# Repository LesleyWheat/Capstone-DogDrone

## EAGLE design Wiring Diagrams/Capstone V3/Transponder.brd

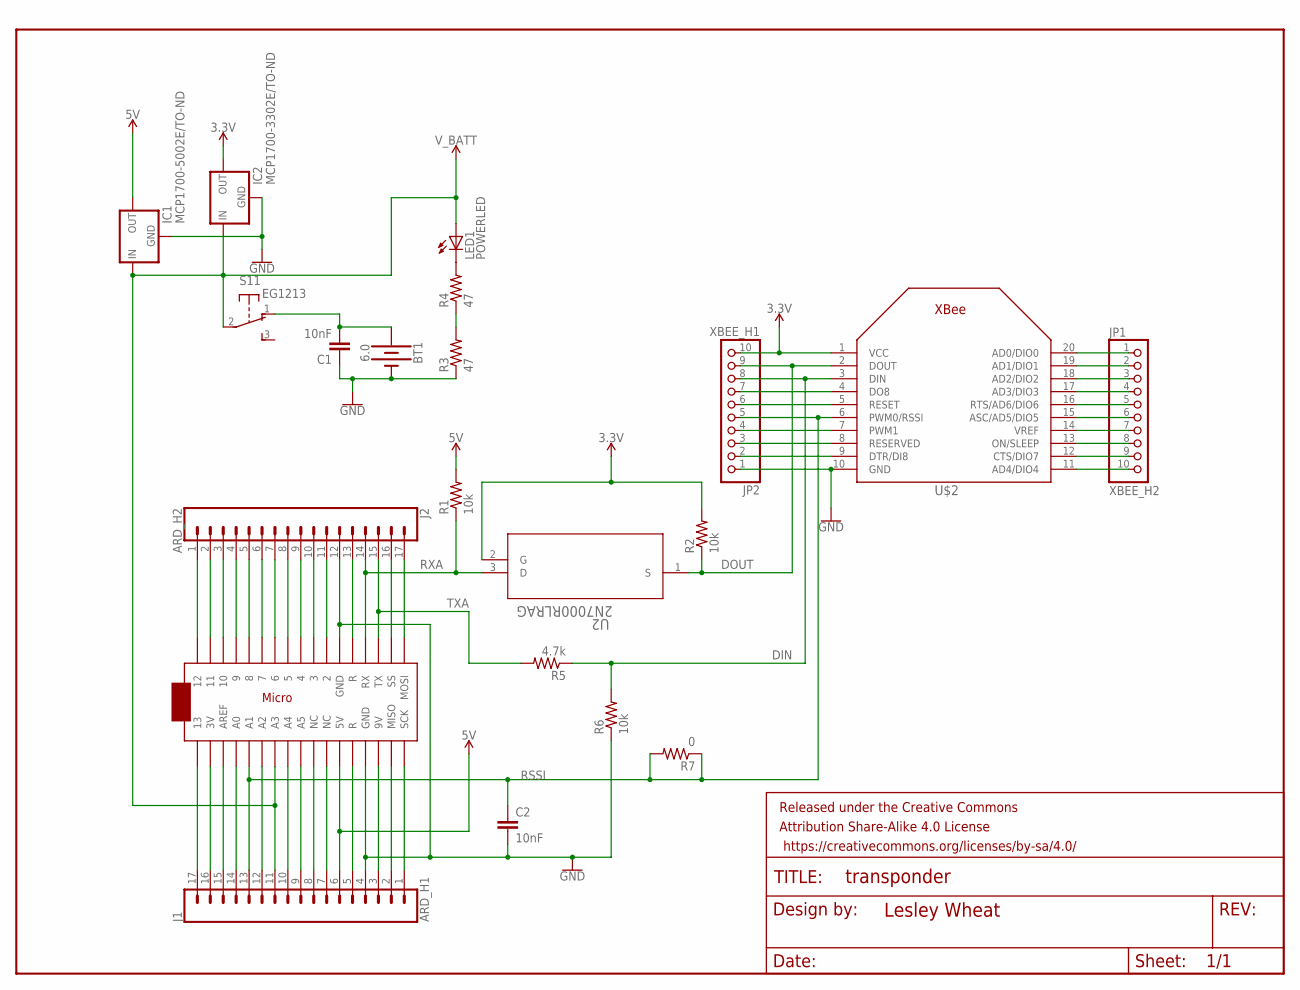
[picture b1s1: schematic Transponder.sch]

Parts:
BT1: 6.0; BATTCON_20MM_4LEGS
C1, C2: 10nF; CAP-PTH-10MM
FRAME1: FRAME-LETTERNO_PACKAGE; DUMMY
IC1: MCP1700-5002E/TO-ND; TO92-INLINE
IC2: MCP1700-3302E/TO-ND; TO92-INLINE
J1: ARD_H1; 1X17_NO_SILK
J2: ARD_H2; 1X17_NO_SILK
JP1: XBEE_H2; 1X10M
JP2: XBEE_H1; 1X10M
LED1: POWERLED; LED5MM
R1, R2, R6: 10k; 0207/12
R3, R4: 47; 0207/12
R5: 4.7k; 0207/12
R7: 0; 0207/12
S1: EG1213
U2: 2N7000RLRAG; TO-92
U$1: ARDUINOMICRO
U$2: XBEE

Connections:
3.3V: IC2.3 (OUT), JP2.10, R2.2, U2.2 (G), U$2.1 (VCC)
5V: IC1.3 (OUT), J1.6, R1.2, U$1.P$23 (5V)
DIN: JP2.8, R5.1, R6.2, U$2.3 (DIN)
DOUT: JP2.9, R2.1, U2.1 (S), U$2.2 (DOUT)
GND: BT1.NEGATIVE (-), C1.1, C2.2, IC1.1 (GND), IC2.1 (GND), J1.4, J2.12, JP2.1, R3.1, R6.1, U$1.P$12 (GND), U$1.P$21 (GND), U$2.10 (GND)
unnamed: BT1.POSITIVE@1 (+), BT1.POSITIVE@2 (+), BT1.POSITIVE@3 (+), BT1.POSITIVE@4 (+), C1.2, S1.1 (O)
unnamed: JP2.3, U$2.8 (RESERVED)
unnamed: J1.14, U$1.P$31 (A0)
unnamed: LED1.K (C), R4.2
unnamed: R3.2, R4.1
unnamed: J1.17, U$1.P$34 (13)
unnamed: J1.15, U$1.P$32 (AREF)
unnamed: J1.12, U$1.P$29 (A2)
unnamed: J1.9, U$1.P$26 (A5)
unnamed: J1.10, U$1.P$27 (A4)
unnamed: J1.8, U$1.P$25 (NC)
unnamed: J1.7, U$1.P$24 (NC)
unnamed: J1.5, U$1.P$13 (R)
unnamed: J1.3, U$1.P$20 (9V)
unnamed: J1.2, U$1.P$19 (MISO)
unnamed: J1.1, U$1.P$18 (SCK)
unnamed: J2.17, U$1.P$17 (MOSI)
unnamed: J2.16, U$1.P$16 (SS)
unnamed: J2.13, U$1.P$22 (R)
unnamed: J2.11, U$1.P$11 (2)
unnamed: J2.10, U$1.P$10 (3)
unnamed: J2.9, U$1.P$9 (4)
unnamed: J2.7, U$1.P$7 (6)
unnamed: J2.8, U$1.P$8 (5)
unnamed: JP1.1, U$2.20 (AD0/DIO0)
unnamed: J2.6, U$1.P$6 (7)
unnamed: J2.5, U$1.P$5 (8)
unnamed: J2.4, U$1.P$4 (9)
unnamed: J2.3, U$1.P$3 (10)
unnamed: J2.2, U$1.P$2 (11)
unnamed: J2.1, U$1.P$1 (12)
unnamed: J1.16, U$1.P$33 (3V)
unnamed: JP1.2, U$2.19 (AD1/DIO1)
unnamed: JP1.3, U$2.18 (AD2/DIO2)
unnamed: JP1.4, U$2.17 (AD3/DIO3)
unnamed: JP1.5, U$2.16 (RTS/AD6/DIO6)
unnamed: JP1.6, U$2.15 (ASC/AD5/DIO5)
unnamed: JP1.7, U$2.14 (VREF)
unnamed: JP1.8, U$2.13 (ON/SLEEP)
unnamed: JP1.9, U$2.12 (CTS/DIO7)
unnamed: JP1.10, U$2.11 (AD4/DIO4)
unnamed: JP2.2, U$2.9 (DTR/DI8)
unnamed: JP2.4, U$2.7 (PWM1)
unnamed: JP2.6, U$2.5 (RESET)
unnamed: JP2.7, U$2.4 (DO8)
RSSI: C2.1, J1.13, JP2.5, R7.1, R7.2, U$1.P$30 (A1), U$2.6 (PWM0/RSSI)
RXA: J2.14, R1.1, U2.3 (D), U$1.P$14 (RX)
TXA: J2.15, R5.2, U$1.P$15 (TX)
V_BATT: IC1.2 (IN), IC2.2 (IN), J1.11, LED1.A, S1.2, U$1.P$28 (A3)

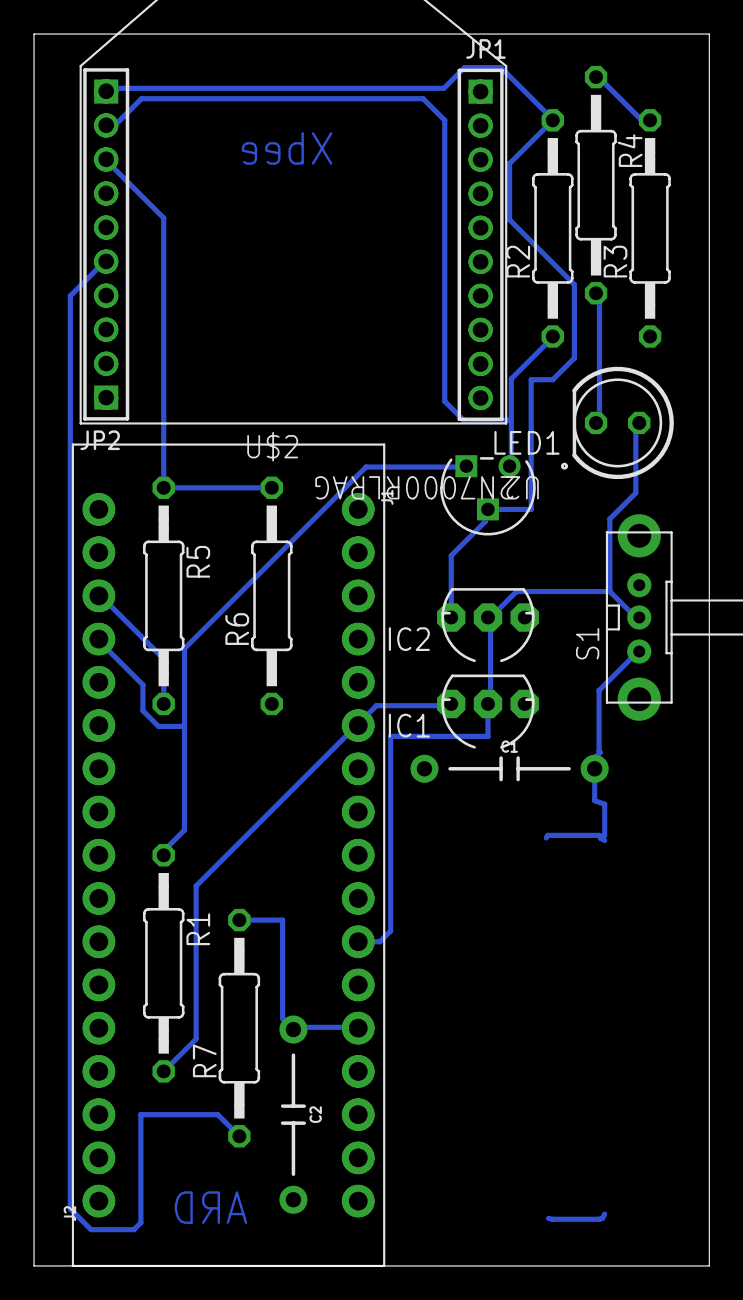
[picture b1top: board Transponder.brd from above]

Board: 2 copper layers, 39.7 x 72.4 mm, 22 parts (1 on the bottom side), 54 nets.

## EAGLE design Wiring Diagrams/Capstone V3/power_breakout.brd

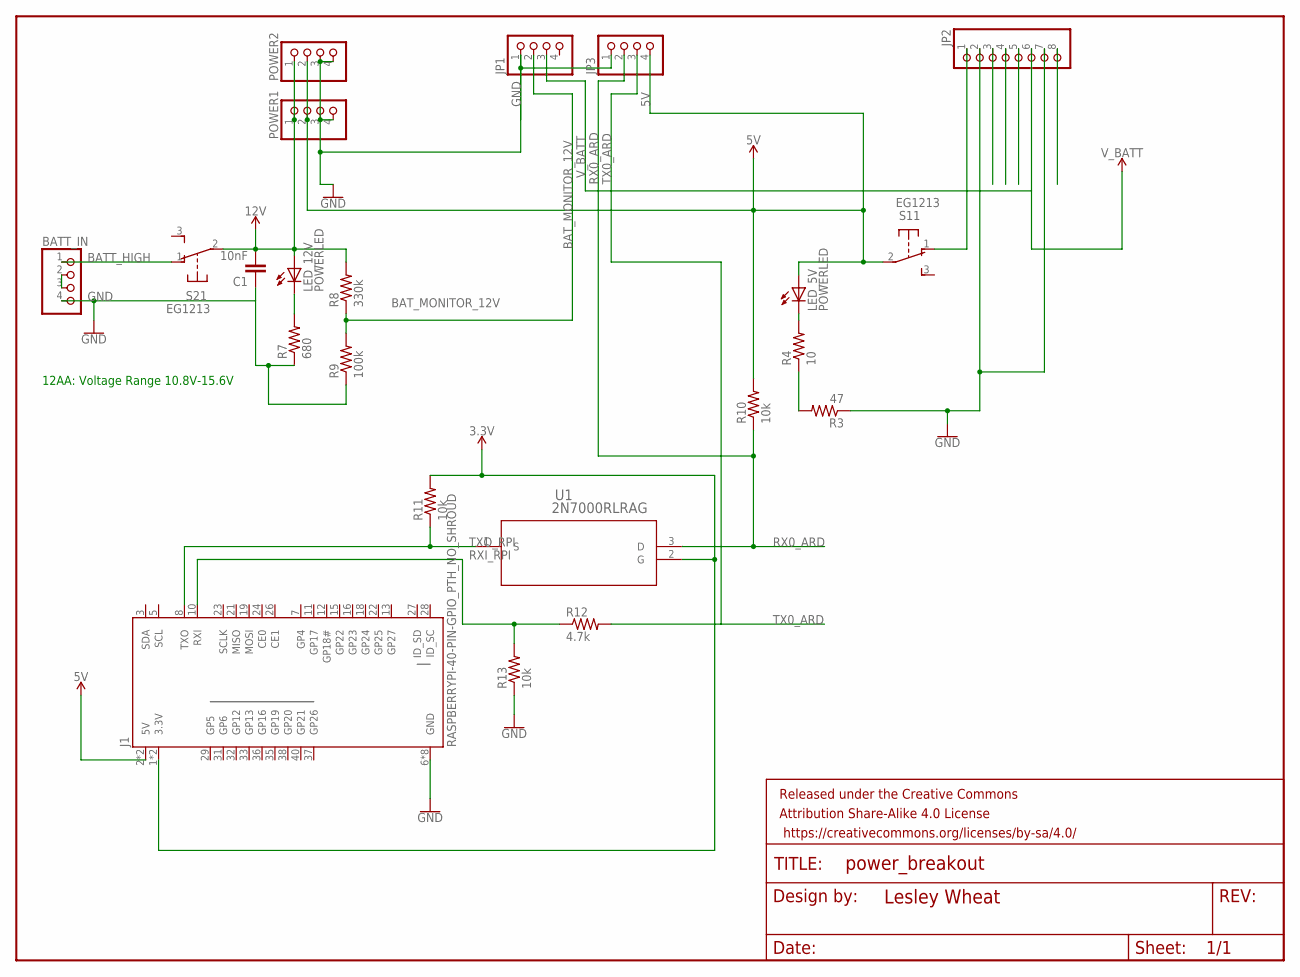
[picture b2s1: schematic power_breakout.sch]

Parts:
BATT_IN: PINHD-1X4; 1X04
C1: 10nF; CAP-PTH-10MM
FRAME1: FRAME-LETTERNO_PACKAGE; DUMMY
J1: RASPBERRYPI-40-PIN-GPIO_PTH_NO_SHROUD; 2X20
JP1, JP3: PINHD-1X4; 1X04
JP2: PINHD-1X8; 1X08
LED_5V, LED_12V: POWERLED; LED5MM
POWER1, POWER2: PINHD-1X4; 1X04
R3: 47; 0207/12
R4: 10; 0207/12
R7: 680; 0207/12
R8: 330k; 0207/12
R9: 100k; 0207/12
R10, R11, R13: 10k; 0207/12
R12: 4.7k; 0207/12
S1, S2: EG1213
U1: 2N7000RLRAG; TO-92

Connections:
3.3V: J1.1 (3.3V), J1.17 (3.3V), R11.2, U1.2 (G)
5V: J1.2 (5V), J1.4 (5V), JP3.4, LED_5V.A, POWER1.2, POWER2.2, R10.2, S1.2
12V: C1.2, LED_12V.A, POWER1.1, POWER2.1, R8.2, S2.2
BATT_HIGH: BATT_IN.1, S2.1 (O)
BAT_MONITOR_12V: JP1.2, R8.1, R9.2
GND: BATT_IN.4, C1.1, J1.6 (GND), J1.9 (GND), J1.14 (GND), J1.20 (GND), J1.25 (GND), J1.30 (GND), J1.34 (GND), J1.39 (GND), JP1.1, JP2.2, JP2.7, JP3.1, POWER1.3, POWER1.4, POWER2.3, POWER2.4, R3.1, R7.1, R9.1, R13.1
unnamed: BATT_IN.2, BATT_IN.3
unnamed: LED_12V.K (C), R7.2
unnamed: JP2.1, S1.1 (O)
unnamed: LED_5V.K (C), R4.2
unnamed: R3.2, R4.1
RX0_ARD: JP3.2, R10.1, U1.3 (D)
RXI_RPI: J1.10 (RXI), R12.1, R13.2
TX0_ARD: JP3.3, R12.2
TXO_RPI: J1.8 (TXO), R11.1, U1.1 (S)
V_BATT: JP1.3, JP2.6

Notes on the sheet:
12AA: Voltage Range 10.8V-15.6V

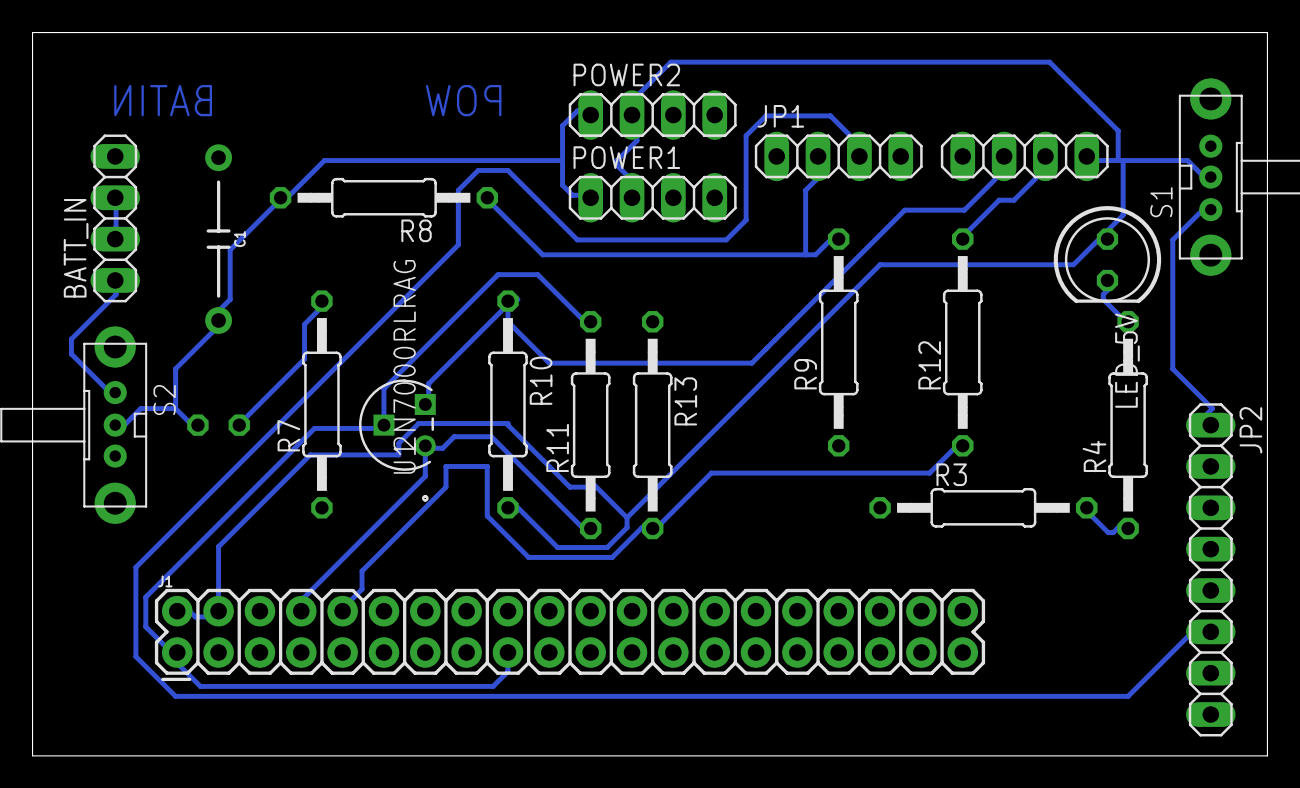
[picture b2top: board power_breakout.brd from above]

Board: 2 copper layers, 75.9 x 44.4 mm, 23 parts (1 on the bottom side), 16 nets.

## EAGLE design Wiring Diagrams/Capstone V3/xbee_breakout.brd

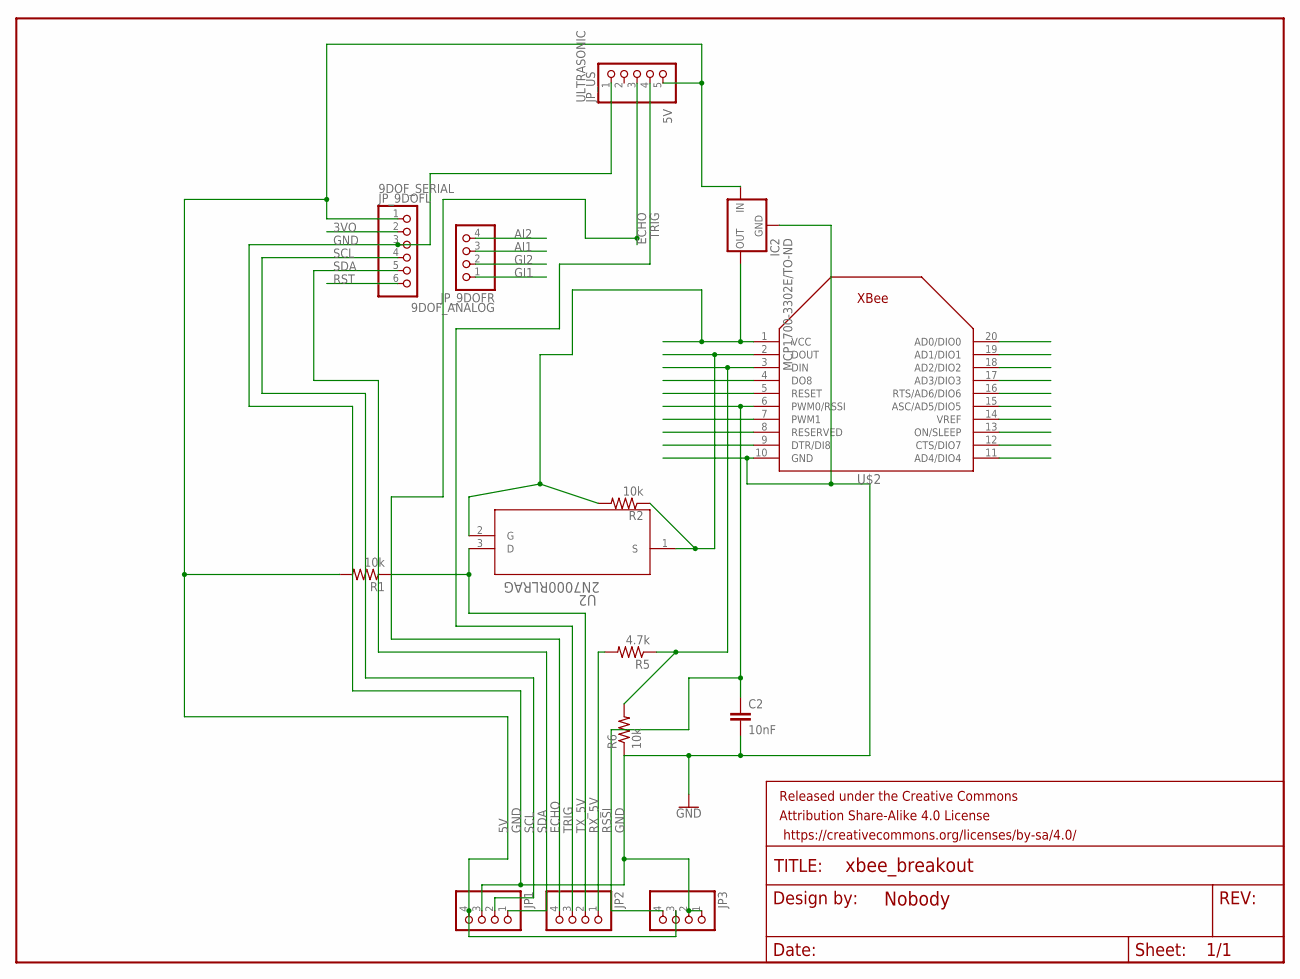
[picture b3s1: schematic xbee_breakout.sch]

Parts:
C2: 10nF; CAP-PTH-10MM
FRAME1: FRAME-LETTERNO_PACKAGE; DUMMY
IC2: MCP1700-3302E/TO-ND; TO92-INLINE
JP1, JP2, JP3: PINHD-1X4; 1X04
JP_9DOFL: PINHD-1X6; 1X06
JP_9DOFR: PINHD-1X4; 1X04
JP_US: PINHD-1X5; 1X05
R1, R2, R6: 10k; 0207/12
R5: 4.7k; 0207/12
U2: 2N7000RLRAG; TO-92
U$2: XBEE

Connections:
3VO: JP_9DOFL.2
5V: IC2.2 (IN), JP1.4, JP3.3, JP_9DOFL.1, JP_US.5, R1.2
AI1: JP_9DOFR.3
AI2: JP_9DOFR.4
DIN: R5.1, R6.2, U$2.3 (DIN)
DOUT: R2.1, U2.1 (S), U$2.2 (DOUT)
ECHO: JP2.4, JP_US.3
GI1: JP_9DOFR.1
GI2: JP_9DOFR.2
GND: C2.2, IC2.1 (GND), JP1.3, JP3.1, JP3.2, JP_9DOFL.3, JP_US.1, R6.1, U$2.10 (GND)
RSSI: C2.1, JP3.4, U$2.6 (PWM0/RSSI)
RST: JP_9DOFL.6
RX_5V: JP2.1, R5.2
SCL: JP1.2, JP_9DOFL.4
SDA: JP1.1, JP_9DOFL.5
TRIG: JP2.3, JP_US.4
TX_5V: JP2.2, R1.1, U2.3 (D)
VCC: IC2.3 (OUT), R2.2, U2.2 (G), U$2.1 (VCC)

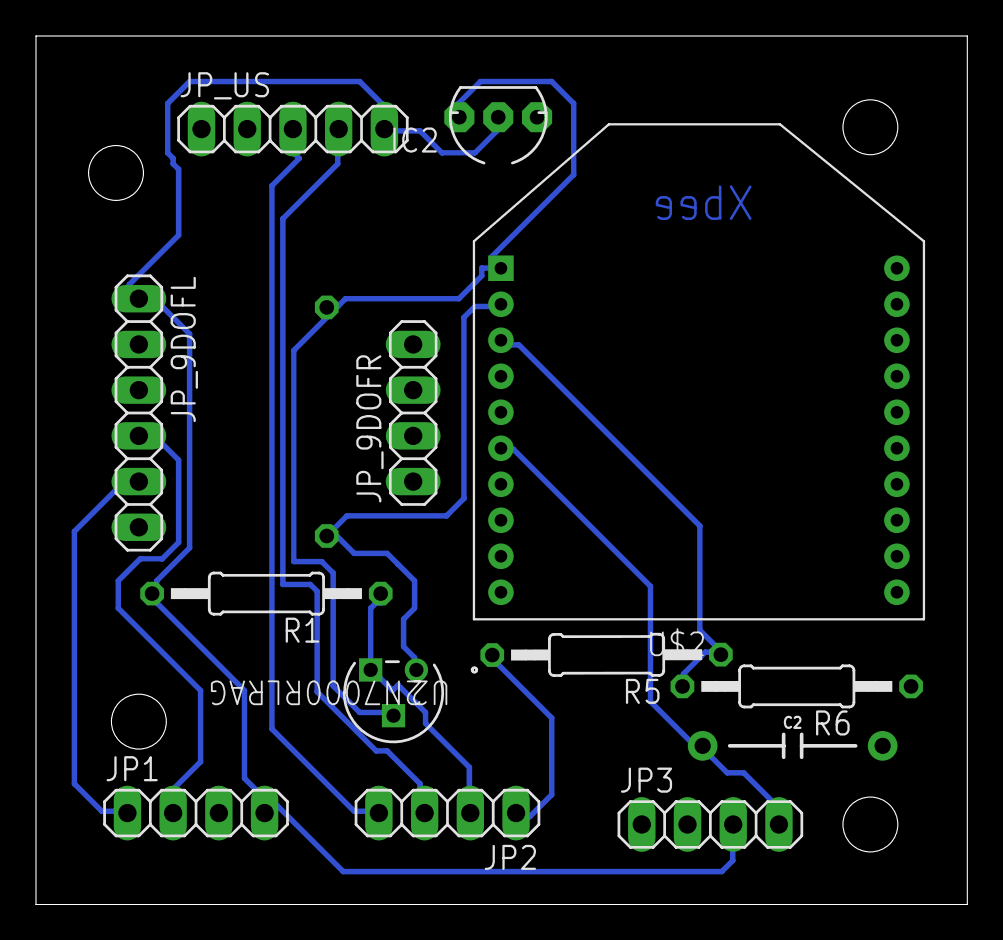
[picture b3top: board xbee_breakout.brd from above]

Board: 2 copper layers, 51.7 x 48.2 mm, 15 parts (1 on the bottom side), 12 nets.

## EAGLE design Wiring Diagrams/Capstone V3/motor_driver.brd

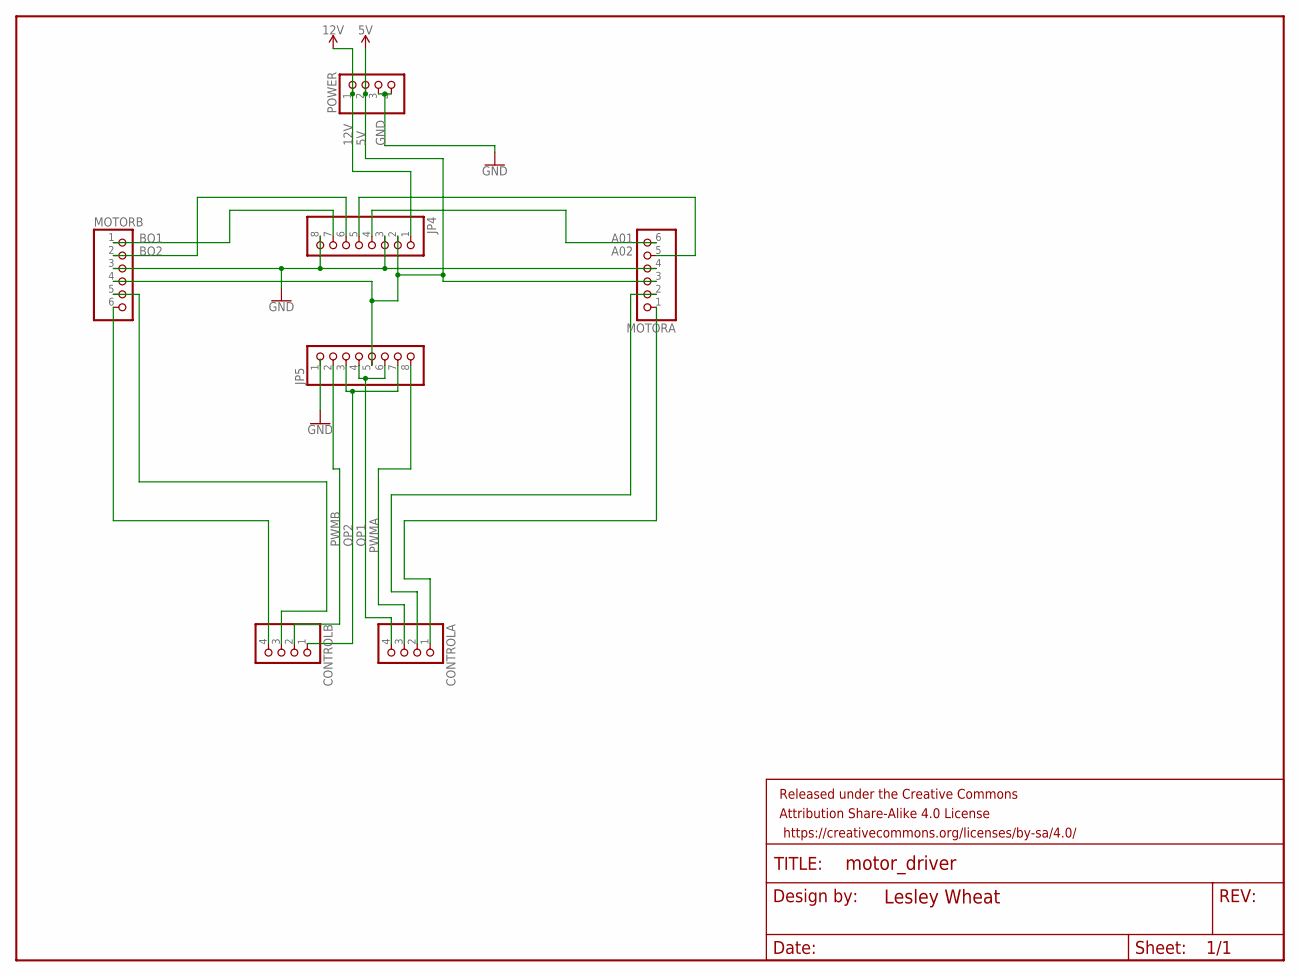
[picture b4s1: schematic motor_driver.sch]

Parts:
CONTROLA: PINHD-1X4; 1X04
CONTROLB: PINHD-1X4; 1X04
FRAME2: FRAME-LETTERNO_PACKAGE; DUMMY
JP4, JP5: PINHD-1X8; 1X08
MOTORA: PINHD-1X6; 1X06
MOTORB: PINHD-1X6; 1X06
POWER: PINHD-1X4; 1X04

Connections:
5V: JP4.2, JP5.5, MOTORA.3, MOTORB.4, POWER.2
12V: JP4.1, POWER.1
A01: JP4.4, MOTORA.6
A02: JP4.5, MOTORA.5
BO1: JP4.7, MOTORB.1
BO2: JP4.6, MOTORB.2
GND: JP4.3, JP4.8, JP5.1, MOTORA.4, MOTORB.3, POWER.3, POWER.4
unnamed: CONTROLB.4, MOTORB.6
unnamed: CONTROLA.1, MOTORA.1
unnamed: CONTROLB.3, MOTORB.5
unnamed: CONTROLA.2, MOTORA.2
OP1: CONTROLA.4, JP5.4, JP5.6
OP2: CONTROLB.1, JP5.3, JP5.7
PWMA: CONTROLA.3, JP5.8
PWMB: CONTROLB.2, JP5.2

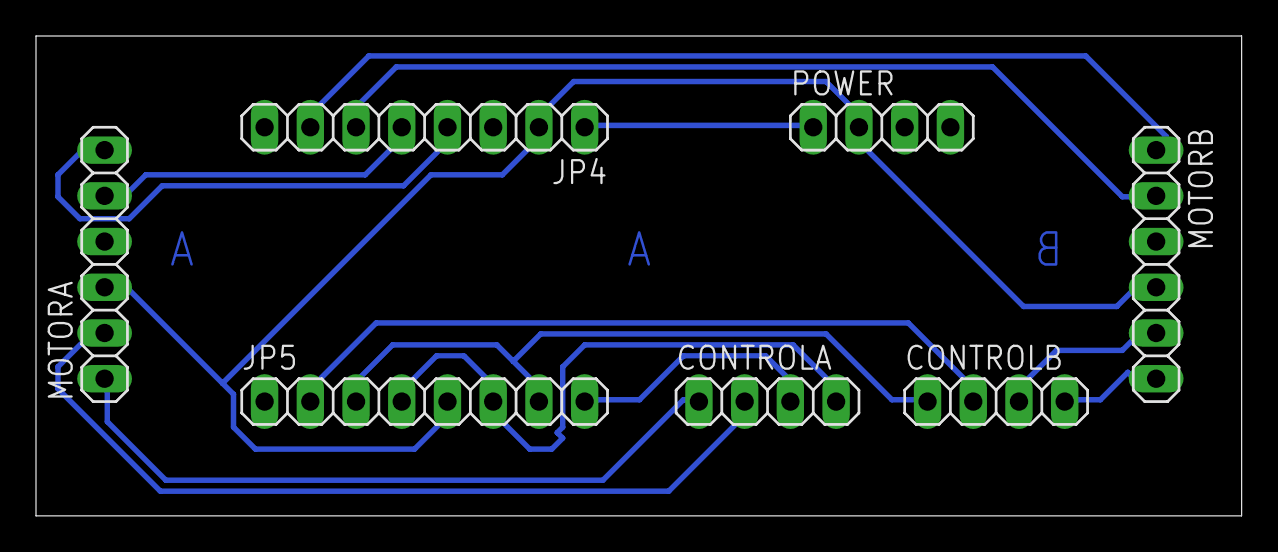
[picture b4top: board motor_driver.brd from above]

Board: 2 copper layers, 67.0 x 26.7 mm, 8 parts (0 on the bottom side), 15 nets.

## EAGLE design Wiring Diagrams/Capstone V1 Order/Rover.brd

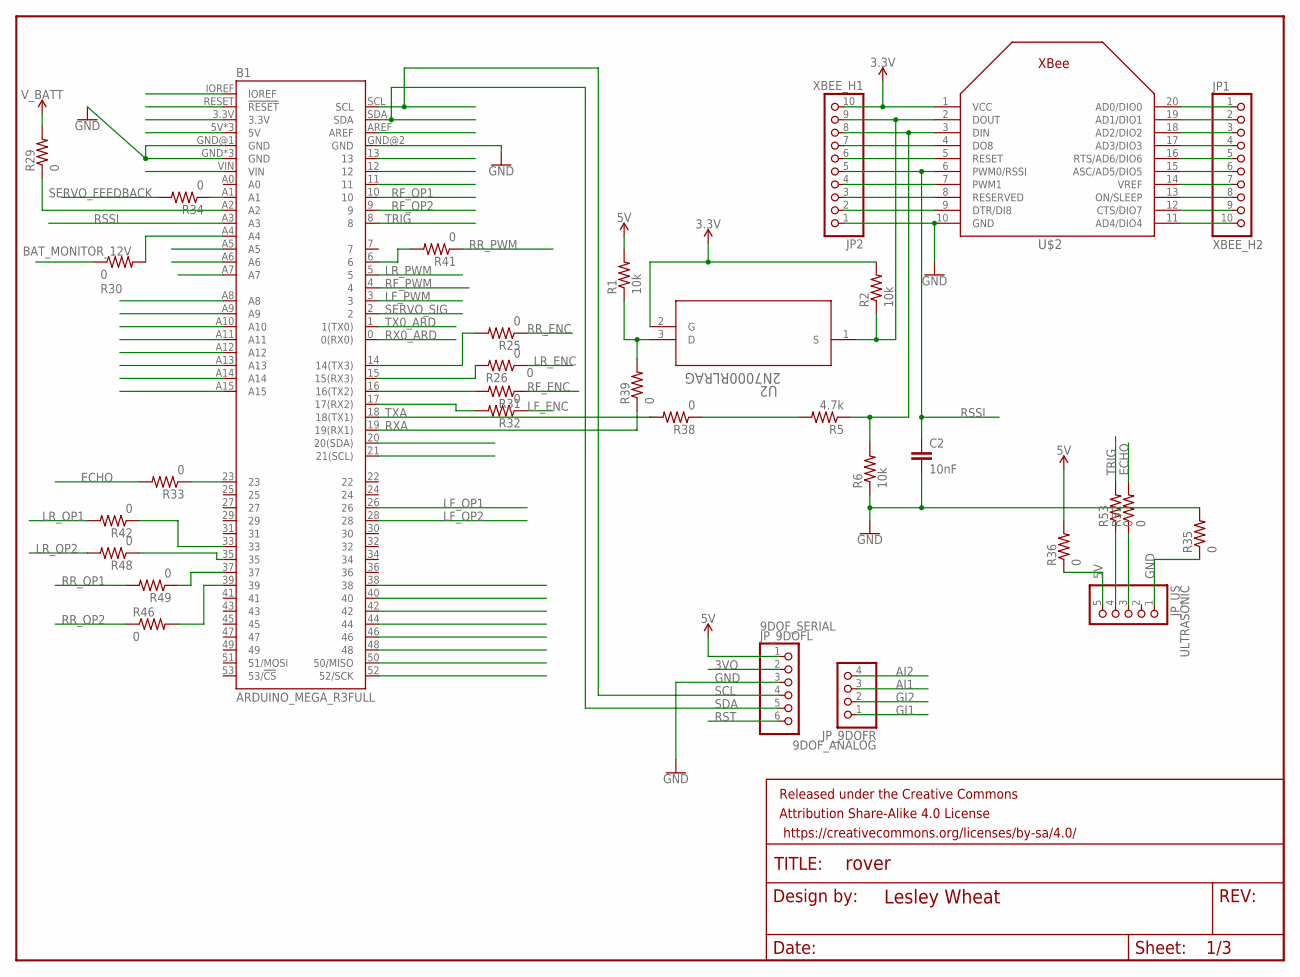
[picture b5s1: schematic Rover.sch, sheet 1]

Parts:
B1: ARDUINO_MEGA_R3FULL; ARDUINO_MEGA_NO_SILK
C2: 10nF; CAP-PTH-10MM
FRAME1: FRAME-LETTERNO_PACKAGE; DUMMY
JP1: XBEE_H2; 1X10M
JP2: XBEE_H1; 1X10M
JP_9DOFL: PINHD-1X6; 1X06
JP_9DOFR: PINHD-1X4; 1X04
JP_US: PINHD-1X5; 1X05
R1, R2, R6: 10k; 0207/12
R5: 4.7k; 0207/12
R25, R26, R29, R30, R31, R32, R33, R34, R35, R36, R38, R39, R41, R42, R46, R48, R49, R52, R53: 0; 0207/12
U2: 2N7000RLRAG; TO-92
U$2: XBEE

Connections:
3.3V: JP2.10, R2.2, U2.2 (G), U$2.1 (VCC); also elsewhere on the board
3VO: JP_9DOFL.2
5V: JP_9DOFL.1, R1.2, R36.2; also elsewhere on the board
AI1: JP_9DOFR.3
AI2: JP_9DOFR.4
BAT_MONITOR_12V: R30.1; also elsewhere on the board
DIN: JP2.8, R5.1, R6.2, U$2.3 (DIN)
DOUT: JP2.9, R2.1, U2.1 (S), U$2.2 (DOUT)
ECHO: R33.2, R52.2
GI1: JP_9DOFR.1
GI2: JP_9DOFR.2
GND: B1.GND, B1.GND@1 (GND), B1.GND@2 (GND), B1.GND@3 (GND), B1.GND@4 (GND), C2.2, JP2.1, JP_9DOFL.3, R6.1, R35.2, U$2.10 (GND); also elsewhere on the board
LF_ENC: R32.1; also elsewhere on the board
LF_OP1: B1.26; also elsewhere on the board
LF_OP2: B1.28; also elsewhere on the board
LF_PWM: B1.3; also elsewhere on the board
LR_ENC: R26.1; also elsewhere on the board
LR_OP1: R42.2; also elsewhere on the board
LR_OP2: R48.2; also elsewhere on the board
LR_PWM: B1.5; also elsewhere on the board
unnamed: JP2.3, U$2.8 (RESERVED)
unnamed: B1.6, R41.2
unnamed: B1.5V, B1.5V@1 (5V), B1.5V@2 (5V)
unnamed: JP_US.1, R35.1
unnamed: JP1.1, U$2.20 (AD0/DIO0)
unnamed: B1.39, R46.2
unnamed: JP1.2, U$2.19 (AD1/DIO1)
unnamed: JP1.3, U$2.18 (AD2/DIO2)
unnamed: JP1.4, U$2.17 (AD3/DIO3)
unnamed: JP1.5, U$2.16 (RTS/AD6/DIO6)
unnamed: JP1.6, U$2.15 (ASC/AD5/DIO5)
unnamed: JP1.7, U$2.14 (VREF)
unnamed: JP1.8, U$2.13 (ON/SLEEP)
unnamed: JP1.9, U$2.12 (CTS/DIO7)
unnamed: JP1.10, U$2.11 (AD4/DIO4)
unnamed: JP2.2, U$2.9 (DTR/DI8)
unnamed: JP2.4, U$2.7 (PWM1)
unnamed: JP2.6, U$2.5 (RESET)
unnamed: JP2.7, U$2.4 (DO8)
unnamed: B1.37, R49.1
unnamed: B1.35, R48.1
unnamed: B1.14 (14(TX3)), R25.2
unnamed: B1.16 (16(TX2)), R31.2
unnamed: B1.A2, R29.1
unnamed: B1.A4, R30.2
unnamed: B1.23, R33.1
unnamed: B1.15 (15(RX3)), R26.2
unnamed: B1.17 (17(RX2)), R32.2
unnamed: B1.A1, R34.1
unnamed: JP_US.5, R36.1
unnamed: R5.2, R38.1
unnamed: R1.1, R39.2, U2.3 (D)
unnamed: B1.33, R42.1
unnamed: JP_US.3, R52.1
unnamed: JP_US.4, R53.1
RF_ENC: R31.1; also elsewhere on the board
RF_OP1: B1.10; also elsewhere on the board
RF_OP2: B1.9; also elsewhere on the board
RF_PWM: B1.4; also elsewhere on the board
RR_ENC: R25.1; also elsewhere on the board
RR_OP1: R49.2; also elsewhere on the board
RR_OP2: R46.1; also elsewhere on the board
RR_PWM: R41.1; also elsewhere on the board
RSSI: B1.A3, C2.1, JP2.5, U$2.6 (PWM0/RSSI)
RST: JP_9DOFL.6
RX0_ARD: B1.0 (0(RX0)); also elsewhere on the board
RXA: B1.19 (19(RX1)), R39.1
SCL: B1.SCL, JP_9DOFL.4
SDA: B1.SDA, JP_9DOFL.5
SERVO_FEEDBACK: R34.2; also elsewhere on the board
SERVO_SIG: B1.2; also elsewhere on the board
TRIG: B1.8, R53.2
TX0_ARD: B1.1 (1(TX0)); also elsewhere on the board
TXA: B1.18 (18(TX1)), R38.2
V_BATT: R29.2; also elsewhere on the board

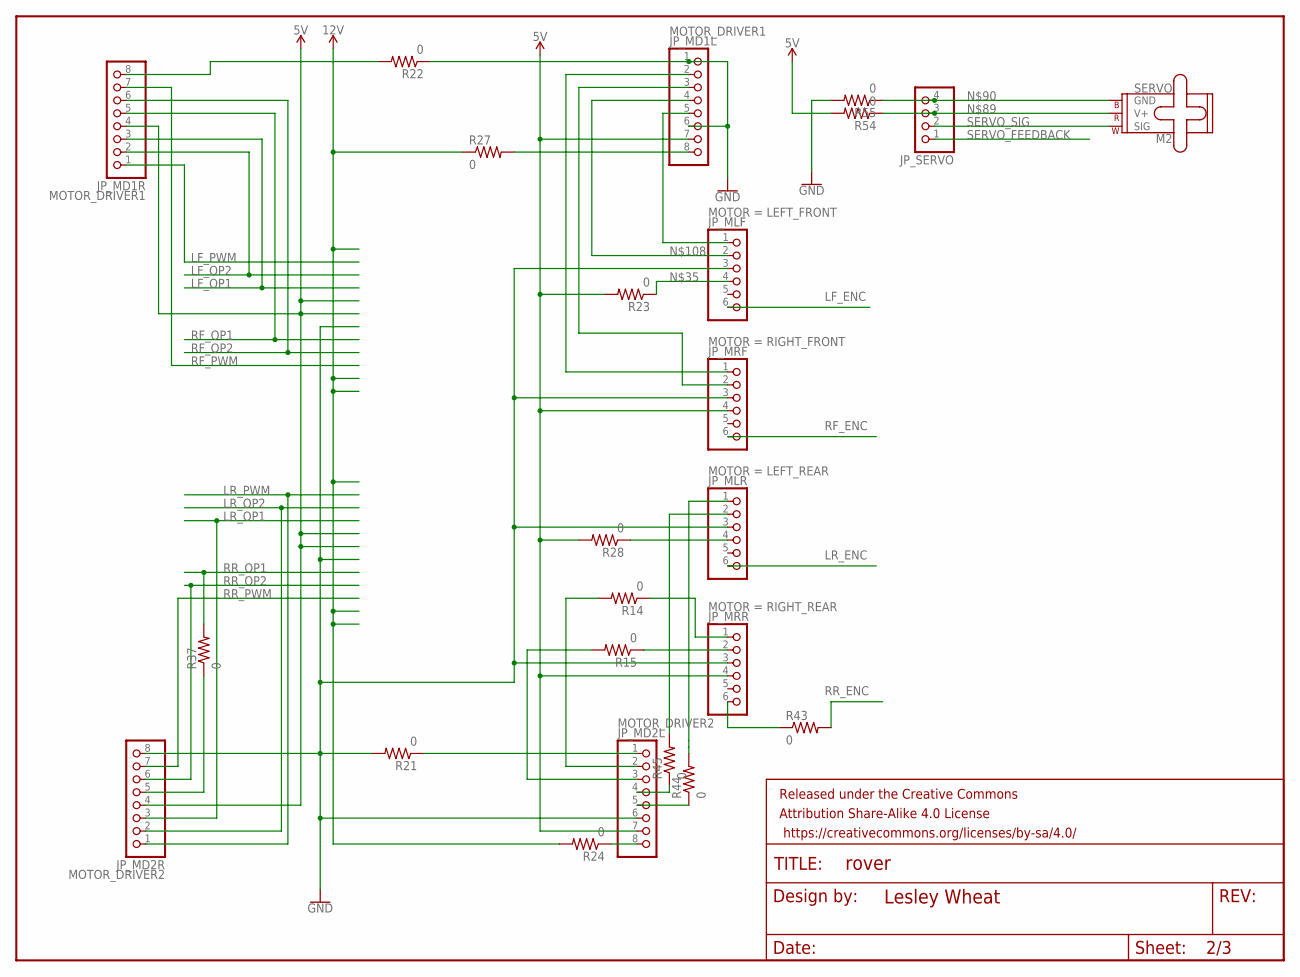
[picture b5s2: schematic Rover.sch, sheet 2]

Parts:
FRAME2: FRAME-LETTERNO_PACKAGE; DUMMY
JP_MD1L, JP_MD1R, JP_MD2L, JP_MD2R: PINHD-1X8; 1X08
JP_MLF: PINHD-1X6; 1X06
JP_MLR: PINHD-1X6; 1X06
JP_MRF: PINHD-1X6; 1X06
JP_MRR: PINHD-1X6; 1X06
JP_SERVO: PINHD-1X4; 1X04
M2: SERVO; 1X03
R14, R15, R21, R22, R23, R24, R27, R28, R37, R43, R44, R45, R54, R55: 0; 0207/12

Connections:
5V: JP_MD1L.7, JP_MD1R.4, JP_MD2L.7, JP_MD2R.4, JP_MRF.4, JP_MRR.4, R23.2, R28.2, R54.2; also elsewhere on the board
12V: R24.2, R27.1; also elsewhere on the board
GND: JP_MD1L.1, JP_MD1L.6, JP_MD2L.6, JP_MD2R.8, JP_MLF.3, JP_MLR.3, JP_MRF.3, JP_MRR.3, R21.2, R22.1, R55.2; also elsewhere on the board
LF_ENC: JP_MLF.6; also elsewhere on the board
LF_OP1: JP_MD1R.3; also elsewhere on the board
LF_OP2: JP_MD1R.2; also elsewhere on the board
LF_PWM: JP_MD1R.1; also elsewhere on the board
LR_ENC: JP_MLR.6; also elsewhere on the board
LR_OP1: JP_MD2R.3; also elsewhere on the board
LR_OP2: JP_MD2R.2; also elsewhere on the board
LR_PWM: JP_MD2R.1; also elsewhere on the board
unnamed: JP_MRR.1, R14.1
unnamed: JP_MRR.2, R15.1
unnamed: JP_MD2L.1, R21.1
unnamed: JP_MD1R.8, R22.2
unnamed: JP_MLF.4, R23.1
unnamed: JP_MD2L.8, R24.1
unnamed: JP_MLR.4, R28.1
unnamed: JP_MD1L.8, R27.2
unnamed: JP_MD2R.5, R37.1
unnamed: JP_MRR.6, R43.1
unnamed: JP_MD2L.4, R45.1
unnamed: JP_MD2L.5, R44.1
unnamed: JP_SERVO.3, M2.2 (V+), R54.1
unnamed: JP_SERVO.4, M2.3 (GND), R55.1
unnamed: JP_MLR.1, R44.2
unnamed: JP_MLR.2, R45.2
unnamed: JP_MD2L.3, R15.2
unnamed: JP_MD2L.2, R14.2
unnamed: JP_MD1L.5, JP_MLF.1
unnamed: JP_MD1L.4, JP_MLF.2
unnamed: JP_MD1L.3, JP_MRF.2
unnamed: JP_MD1L.2, JP_MRF.1
RF_ENC: JP_MRF.6; also elsewhere on the board
RF_OP1: JP_MD1R.5; also elsewhere on the board
RF_OP2: JP_MD1R.6; also elsewhere on the board
RF_PWM: JP_MD1R.7; also elsewhere on the board
RR_ENC: R43.2; also elsewhere on the board
RR_OP1: R37.2; also elsewhere on the board
RR_OP2: JP_MD2R.6; also elsewhere on the board
RR_PWM: JP_MD2R.7; also elsewhere on the board
SERVO_FEEDBACK: JP_SERVO.1; also elsewhere on the board
SERVO_SIG: JP_SERVO.2, M2.1 (SIG); also elsewhere on the board

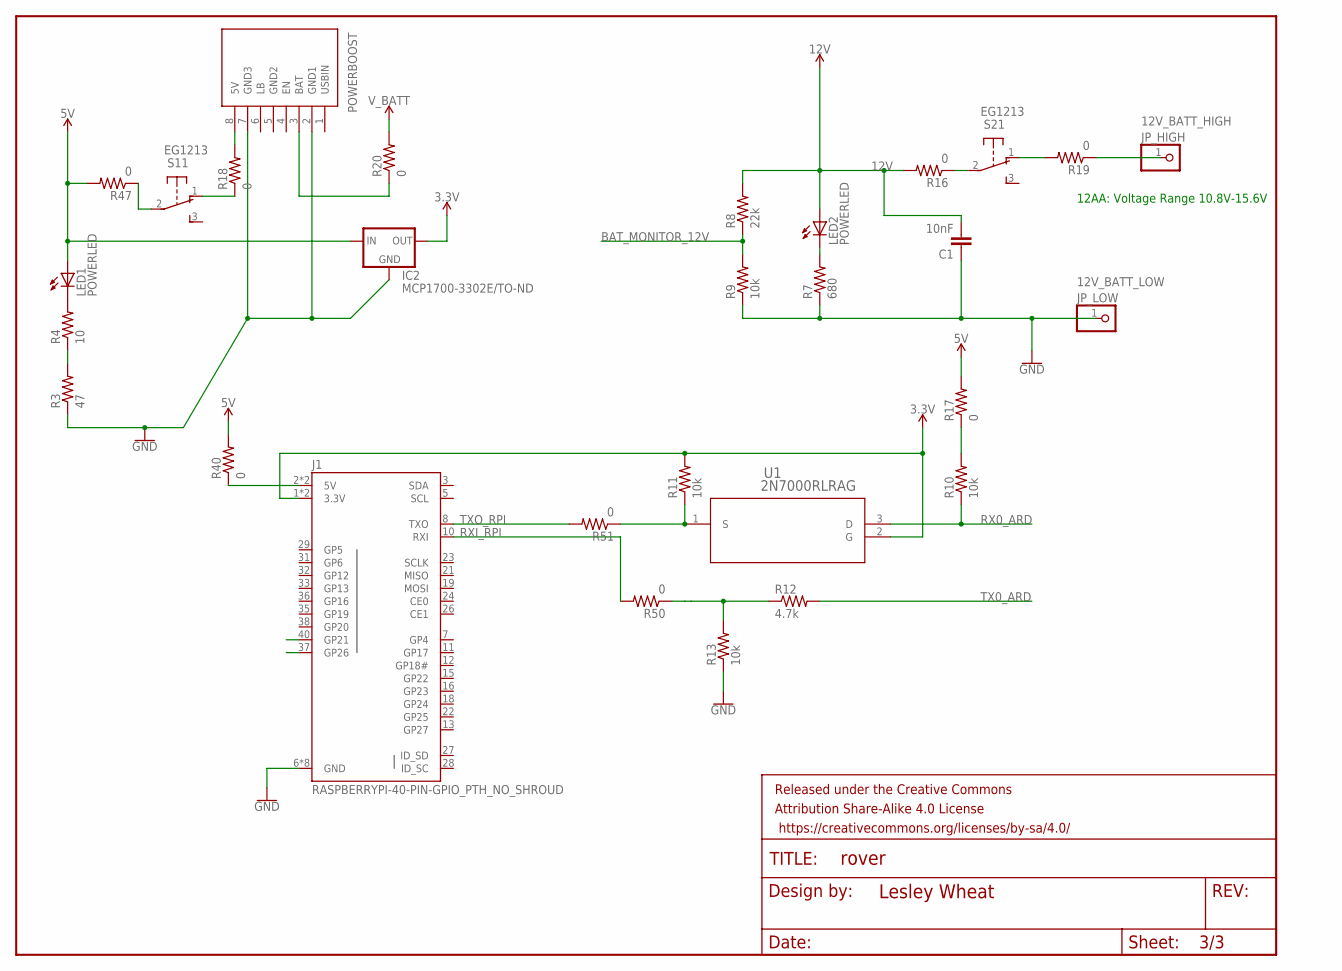
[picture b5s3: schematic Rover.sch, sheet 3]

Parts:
C1: 10nF; CAP-PTH-10MM
FRAME3: FRAME-LETTERNO_PACKAGE; DUMMY
IC2: MCP1700-3302E/TO-ND; TO92-INLINE
J1: RASPBERRYPI-40-PIN-GPIO_PTH_NO_SHROUD; 2X20
JP_HIGH: PINHD-1X1; 1X01
JP_LOW: PINHD-1X1; 1X01
LED1, LED2: POWERLED; LED5MM
R3: 47; 0207/12
R4: 10; 0207/12
R7: 680; 0207/12
R8: 22k; 0207/12
R9, R10, R11, R13: 10k; 0207/12
R12: 4.7k; 0207/12
R16, R17, R18, R19, R20, R40, R47, R50, R51: 0; 0207/12
S1, S2: EG1213
U1: 2N7000RLRAG; TO-92
U$1: POWERBOOST500C; POWERBOOST500

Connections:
3.3V: IC2.3 (OUT), J1.1 (3.3V), J1.17 (3.3V), R11.2, U1.2 (G); also elsewhere on the board
5V: IC2.2 (IN), LED1.A, R17.2, R40.2, R47.2; also elsewhere on the board
12V: C1.2, LED2.A, R8.2, R16.2; also elsewhere on the board
BAT_MONITOR_12V: R8.1, R9.2; also elsewhere on the board
GND: C1.1, IC2.1 (GND), J1.6 (GND), J1.9 (GND), J1.14 (GND), J1.20 (GND), J1.25 (GND), J1.30 (GND), J1.34 (GND), J1.39 (GND), JP_LOW.1, R3.1, R7.1, R9.1, R13.1, U$1.2 (GND1), U$1.7 (GND3); also elsewhere on the board
unnamed: R19.2, S2.1 (O)
unnamed: LED2.K (C), R7.2
unnamed: R10.2, R17.1
unnamed: R18.2, U$1.8 (5V)
unnamed: R16.1, S2.2
unnamed: R18.1, S1.1 (O)
unnamed: JP_HIGH.1, R19.1
unnamed: R20.1, U$1.3 (BAT)
unnamed: R47.1, S1.2
unnamed: R12.1, R13.2, R50.1
unnamed: R11.1, R51.1, U1.1 (S)
unnamed: J1.2 (5V), J1.4 (5V), R40.1
unnamed: LED1.K (C), R4.2
unnamed: R3.2, R4.1
RX0_ARD: R10.1, U1.3 (D); also elsewhere on the board
RXI_RPI: J1.10 (RXI), R50.2
TX0_ARD: R12.2; also elsewhere on the board
TXO_RPI: J1.8 (TXO), R51.2
V_BATT: R20.2; also elsewhere on the board

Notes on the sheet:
12AA: Voltage Range 10.8V-15.6V

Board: 2 copper layers, 88 parts (7 on the bottom side), 108 nets, no tracks yet.

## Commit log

2019-11-08 Start proof of concept arduino side
2019-11-11 Added calibrated madgwick filter
2019-11-11 Added low pass filter
2019-11-12 new cal values
2019-11-12 Removed filter library
2019-11-12 Added motioncal program for calibration
2019-11-12 Updated graph
2019-11-23 Empty files to set up folder system
2019-12-03 Got 2 xbees to communicate to turn on/off led
2019-12-03 Rssi values test
2019-12-14 Xbee test now uses pulsein instead of analogread
2019-12-29 transponder and controller test code is ready, uno sends back float of rssi voltage that is passed through a low pass filter. Micro just needs battery power
2020-01-06 Transponder wiring diagrams
2020-01-06 Reorganized wire diagram files, added rover diagrams
2020-01-06 Small changes to wiring
2020-01-06 Added raspberry pi to wiring diagrams
2020-01-06 Home base and transponder can use the same wiring
2020-01-09 Added encoders to wiring diagram rover and saved to pdf
2020-01-09 Added pdf of transponder/home base wiring diagram
2020-01-17 Created arduino files and objects for project
2020-01-17 Eagle sechmatic small edits
2020-01-18 Updates to xbee test to use with arduino serial plotter
2020-01-19 Complies now
2020-01-20 Reorganized libraries and moved ros to comm module
2020-01-21 Merged files to reduce number, updated cycle time to use us instead of ms, moved battery monitor to diagnostics, setup for encoders, removed setup for motor controls
2020-01-21 Converted static strings to F() to use flash instead of sram, added sram free memory check, defined periods for diagnostics timers, added in extra pins for quad encoder and interrupts, formatiing cha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
2020-01-21 Formatting changes for motor control
2020-01-21 RSSI echo to target and pin reading working
2020-01-22 Added low bound to rpm detection, formating corrections
2020-01-24 Ultrasonic works, memory improvements, start to motor controller
2020-01-27 Motor works by removing the xbee radio and using pins 2 and 3 for interrupt
2020-01-27 Switched variables used in interupts to volatile
2020-01-27 Servo motor pwm with pid control implemented, not tested
2020-02-01 Formatting changes, changed pin map to for arduino mega, xbee rssi added back in
2020-02-03 Updated eagle files, transponder pcb board ready to mill, started rover pcb
2020-02-03 Added gerber files for transponder pcb
2020-02-03 Added datasheets
2020-02-07 Updated wire diagrams for transponder to removed smd
2020-02-07 Added datasheets, made transponder pcb files
2020-02-10 Eagle files added for pcb milling
2020-02-10 Modified power supply board to remove extra holes
2020-02-13 Removed unnessary files
2020-02-17 Added cad models for new rpi4 case
2020-02-18 Pi case stl v1, needs mods
2020-02-18 Changed transponder power source from one CR2032 to two CR2032
2020-02-19 compass examples from https://www.instructables.com/id/Tilt-Compensated-Compass/
2020-02-20 Added test for arduino micro transponder to respond with rssi value
2020-02-22 Uploading stl files for cases
2020-02-22 Arduino file for testing out pin conectivity on boards
2020-03-10 Test file for motors moving
2020-03-12 Added datasheets, pin test moves motors clockwise
2020-03-16 Added schematic and board images so they can be read without downloading eagle
2020-03-16 Added folders for organization
2020-03-21 Changed pin test
2020-03-24 adding initial GUI code
2020-03-24 Updating readme
2020-03-30 Initial Commit - Some changes needed
2020-04-02 Successful pi serial arduino test
2020-04-06 Serial test with 115200 baud
2020-04-08 Changed serial rate to 38400 Globally, needs xbee reconfig from 9600
2020-04-09 Update micro code
2020-04-11 Checkpoint
2020-04-12 Set up comm between pi and arduino and computer to check for set rpm and angle
2020-04-12 Fix buffer overflow
2020-04-13 Motor control over serial but motors keep running
2020-04-14 Test code

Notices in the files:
parts and their libraries:
SparkFun-Boards: Licensing: Creative Commons ShareAlike 4.0 International - https://creativecommons.org/licenses/by-sa/4.0
SparkFun-Aesthetics: Released under the Creative Commons Attribution Share-Alike 4.0 License
SparkFun-Aesthetics: https://creativecommons.org/licenses/by-sa/4.0
